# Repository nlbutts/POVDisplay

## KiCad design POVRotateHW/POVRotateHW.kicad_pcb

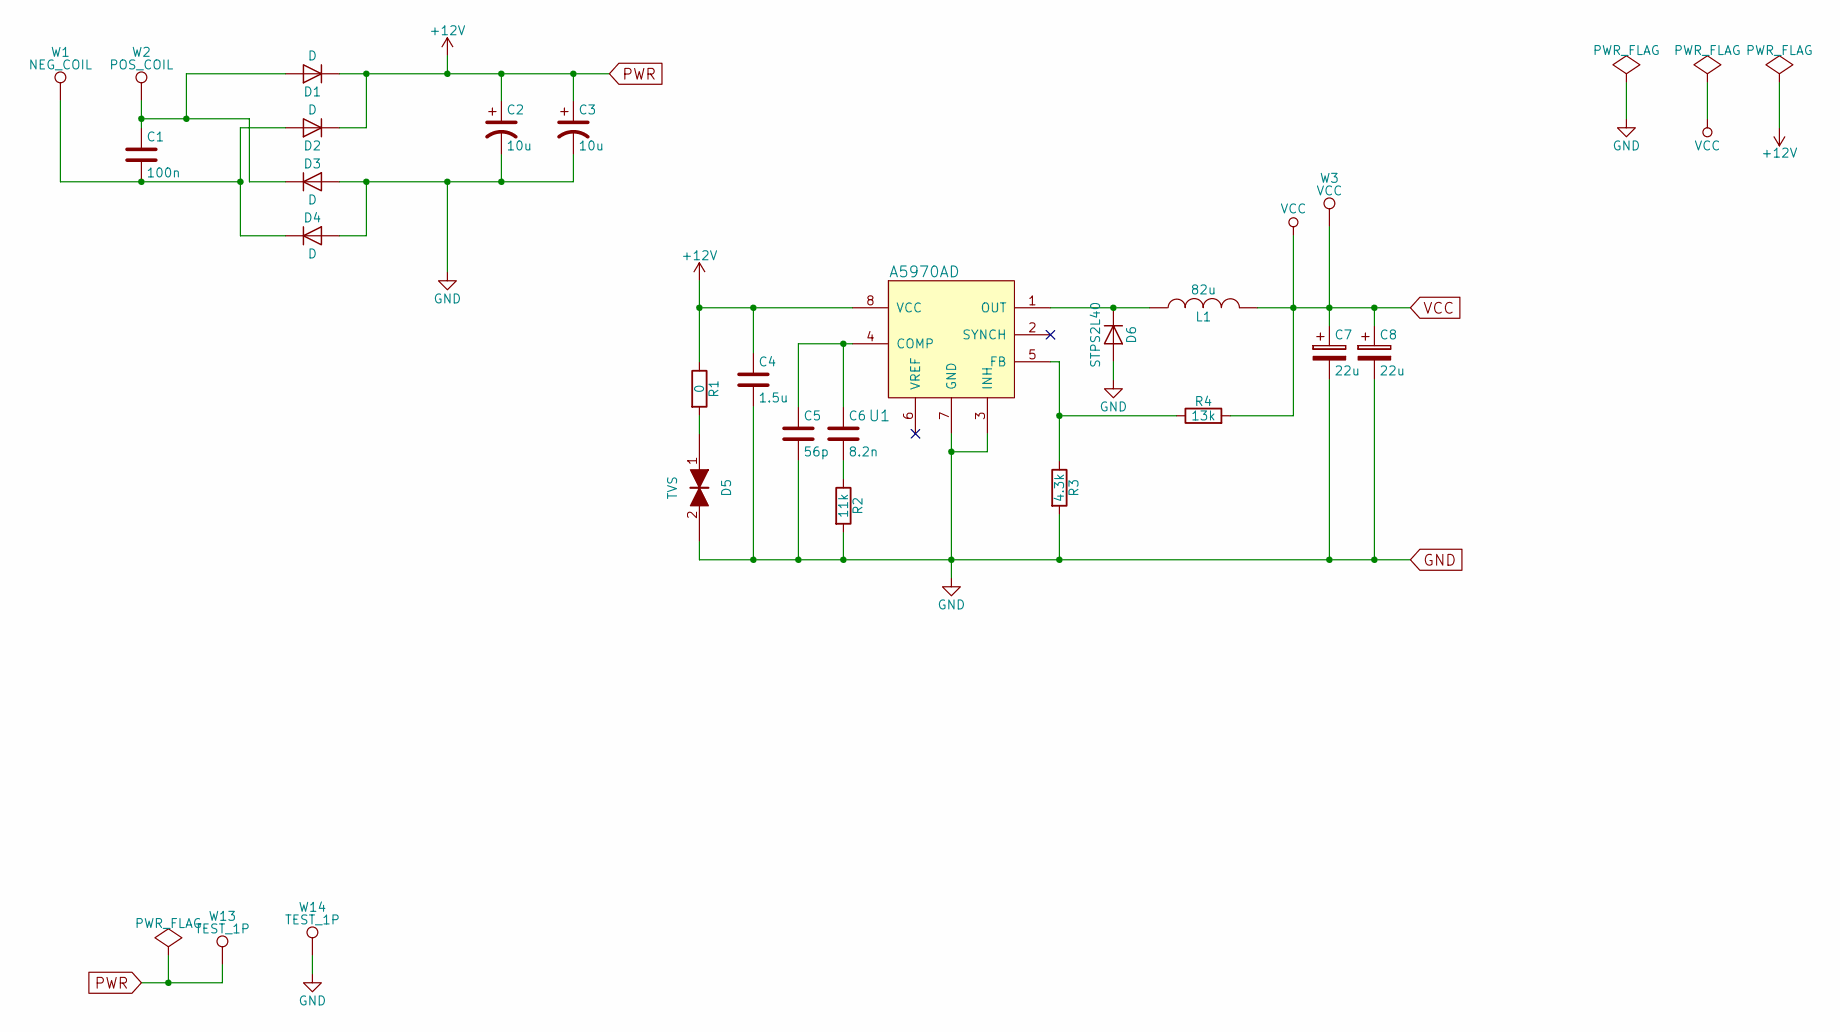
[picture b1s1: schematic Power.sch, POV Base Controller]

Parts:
C1: 100n; C_1210_HandSoldering
C2, C3: 10u; c_elec_5x5.8; PartNum EEE-FT1H220AR; DIGIKEY PCE5022CT-ND
C4: 1.5u; C_0805_HandSoldering; DIGIKEY 445-12701-1-ND
C5: 56p; C_0603_HandSoldering
C6: 8.2n; C_0603_HandSoldering
C7, C8: 22u; SMD-1210_Pol; PartNum TPSB226K006R0375; DIGIKEY 478-9063-1-ND
D1, D2, D3, D4: D; SMB_Handsoldering; PartNum STPS2L40U; DIGIKEY 497-5574-1-ND
D5: TVS; SMB_Handsoldering; PartNum 824520201; DIGIKEY 732-9779-1-ND
D6: STPS2L40; SMB_Handsoldering; PartNum STPS2L40U; DIGIKEY 497-5574-1-ND
L1: 82u; TDK_inductor_12.95x9.4x8.08; PartNum B82476A1104M; Digikey 495-2686-1-ND
R1: 0; R_0603_HandSoldering
R2: 11k; R_0603_HandSoldering
R3: 4.3k; R_0603_HandSoldering
R4: 13k; R_0603_HandSoldering
U1: A5970AD; SOIC-8-N; PartNum A5970ADTR; DIGIKEY 497-10183-1-ND
W1: NEG_COIL; MountingHole_3.2mm_M3_DIN965_Pad
W2: POS_COIL; MountingHole_3.2mm_M3_DIN965_Pad
W3: VCC; Measurement_Point_Round-SMD-Pad_Small
W13, W14: TEST_1P; Measurement_Point_Round-SMD-Pad_Small

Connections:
GND: C2.2, C3.2, C4.2, C5.2, C7.2, C8.2, D3.2 (A), D4.2 (A), D5.2, D6.2 (A), R2.2, R3.2, U1.3 (INH), U1.7 (GND), W14.1; also elsewhere on the board
unnamed: C1.1, D1.2 (A), D3.1 (K), W2.1
unnamed: C1.2, D2.2 (A), D4.1 (K), W1.1
unnamed: C5.1, C6.1, U1.4 (COMP)
unnamed: C6.2, R2.1
unnamed: D5.1, R1.2
unnamed: D6.1 (K), L1.1, U1.1 (OUT)
unnamed: R3.1, R4.1, U1.5 (FB)
PWR: C2.1, C3.1, C4.1, D1.1 (K), D2.1 (K), R1.1, U1.8 (VCC), W13.1; also elsewhere on the board
VCC: C7.1, C8.1, L1.2, R4.2, W3.1; also elsewhere on the board

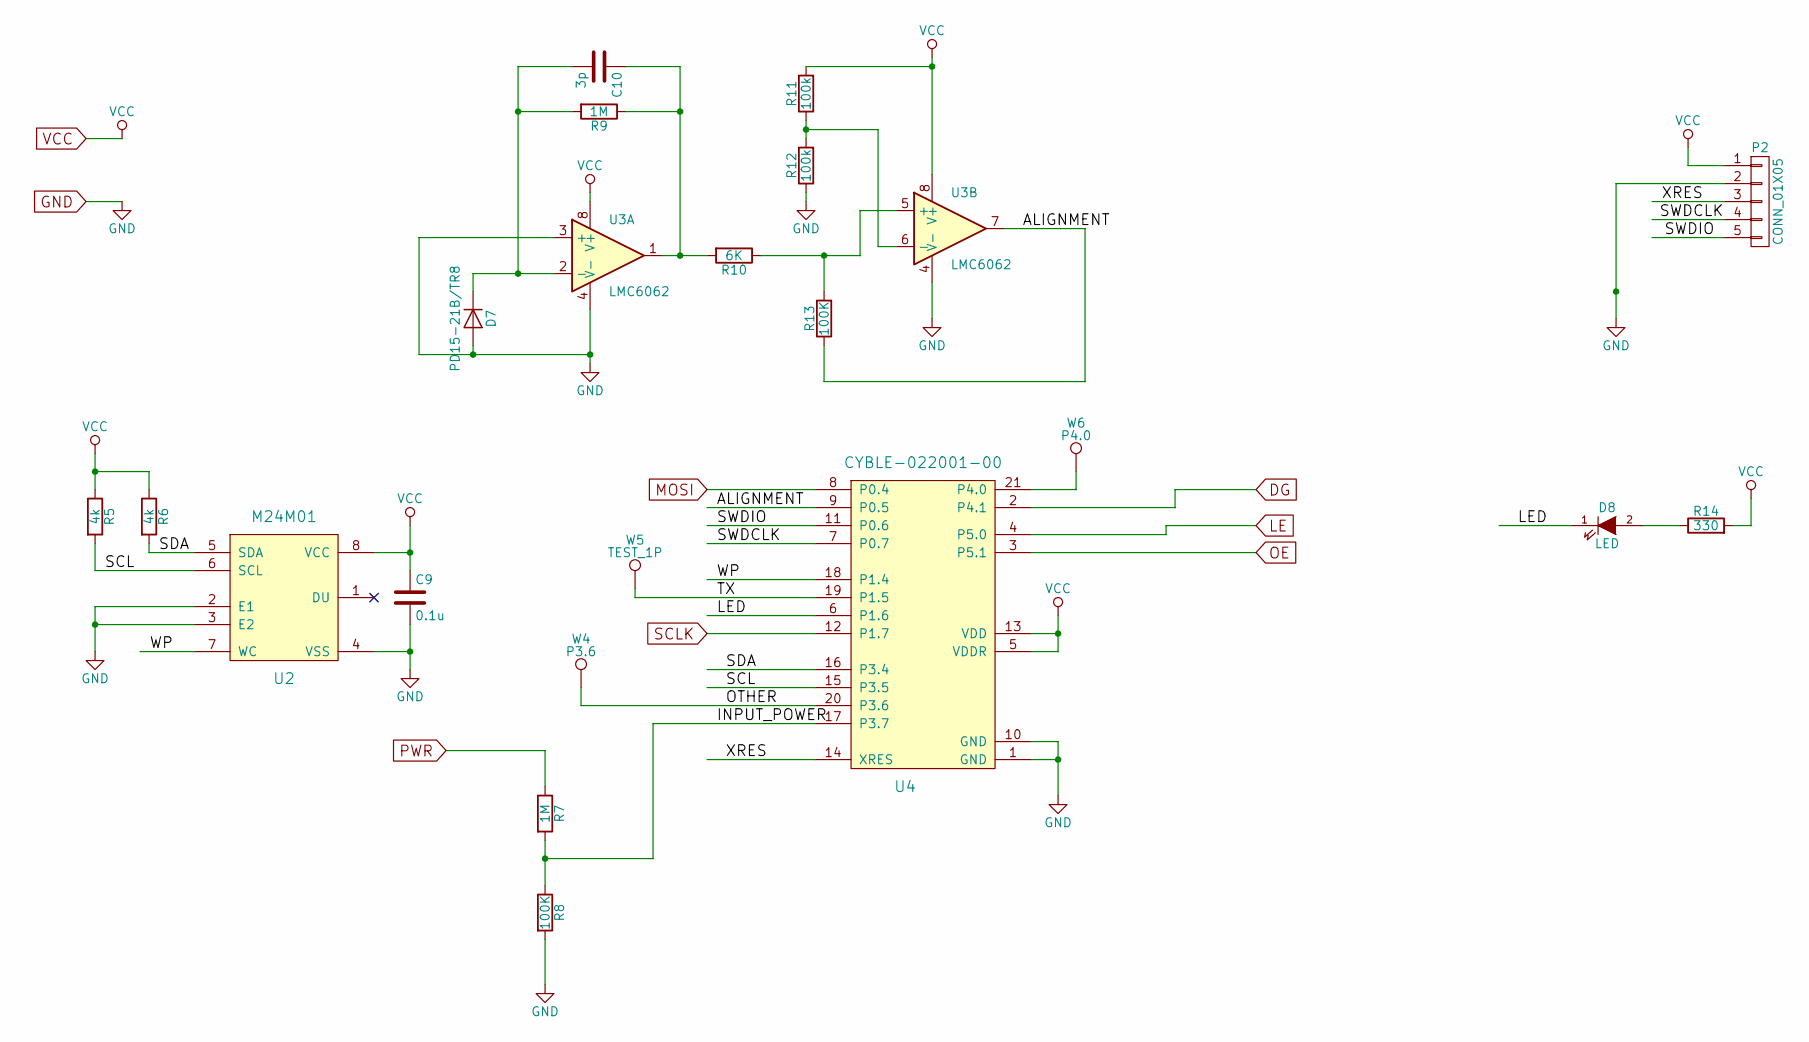
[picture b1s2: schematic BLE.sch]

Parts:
C9: 0.1u; C_0603_HandSoldering
C10: 3p; C_0603_HandSoldering
D7: PD15-21B/TR8; 2-SMD_Z-Bend; DIGIKEY 475-1346-1-ND
D8: LED; LED_0603; PartNum LG L29K-G2J1-24-Z; Digikey 475-2709-1-ND
P2: CONN_01X05; Socket_Strip_Straight_1x05
R5, R6: 4k; R_0603_HandSoldering
R7, R9: 1M; R_0603_HandSoldering
R8, R13: 100K; R_0603_HandSoldering
R10: 6K; R_0603_HandSoldering
R11, R12: 100k; R_0603_HandSoldering
R14: 330; R_0603_HandSoldering
U2: M24M01; SOIC-8-N; PartNum M24M01-RMN6TP; DIGIKEY 497-6351-1-ND
U3: LMC6062; SOIC-8-N; DIGIKEY LMC6032IMX/NOPBCT-ND
U4: CYBLE-022001-00; CYBLE-022001; PartNum CYBLE-022001-00; DIGIKEY 428-3566-PROMO-ND
W4: P3.6; Measurement_Point_Round-SMD-Pad_Small
W5: TEST_1P; Measurement_Point_Round-SMD-Pad_Small
W6: P4.0; Measurement_Point_Round-SMD-Pad_Small

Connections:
/BLE/ALIGNMENT: R13.1, U3.7, U4.9 (P0.5)
/BLE/INPUT_POWER: R7.2, R8.1, U4.17 (P3.7)
/BLE/LED: D8.1 (K), U4.6 (P1.6)
/BLE/OTHER: U4.20 (P3.6), W4.1
/BLE/SCL: R5.2, U2.6 (SCL), U4.15 (P3.5)
/BLE/SDA: R6.2, U2.5 (SDA), U4.16 (P3.4)
/BLE/SWDCLK: P2.4, U4.7 (P0.7)
/BLE/SWDIO: P2.5, U4.11 (P0.6)
/BLE/TX: U4.19 (P1.5), W5.1
/BLE/WP: U2.7 (WC), U4.18 (P1.4)
/BLE/XRES: P2.3, U4.14 (XRES)
DG: U4.2 (P4.1); also elsewhere on the board
GND: C9.2, D7.2 (A), P2.2, R8.2, R12.1, U2.2 (E1), U2.3 (E2), U2.4 (VSS), U3.3 (+), U3.4 (V-), U4.1 (GND), U4.10 (GND); also elsewhere on the board
LE: U4.4 (P5.0); also elsewhere on the board
MOSI: U4.8 (P0.4); also elsewhere on the board
unnamed: C10.1, R9.1, R10.2, U3.1
unnamed: C10.2, D7.1 (K), R9.2, U3.2 (-)
unnamed: D8.2 (A), R14.1
unnamed: R10.1, R13.2, U3.5 (+)
unnamed: R11.1, R12.2, U3.6 (-)
unnamed: U4.21 (P4.0), W6.1
OE: U4.3 (P5.1); also elsewhere on the board
PWR: R7.1; also elsewhere on the board
SCLK: U4.12 (P1.7); also elsewhere on the board
VCC: C9.1, P2.1, R5.1, R6.1, R11.2, R14.2, U2.8 (VCC), U3.8 (V+), U4.5 (VDDR), U4.13 (VDD); also elsewhere on the board

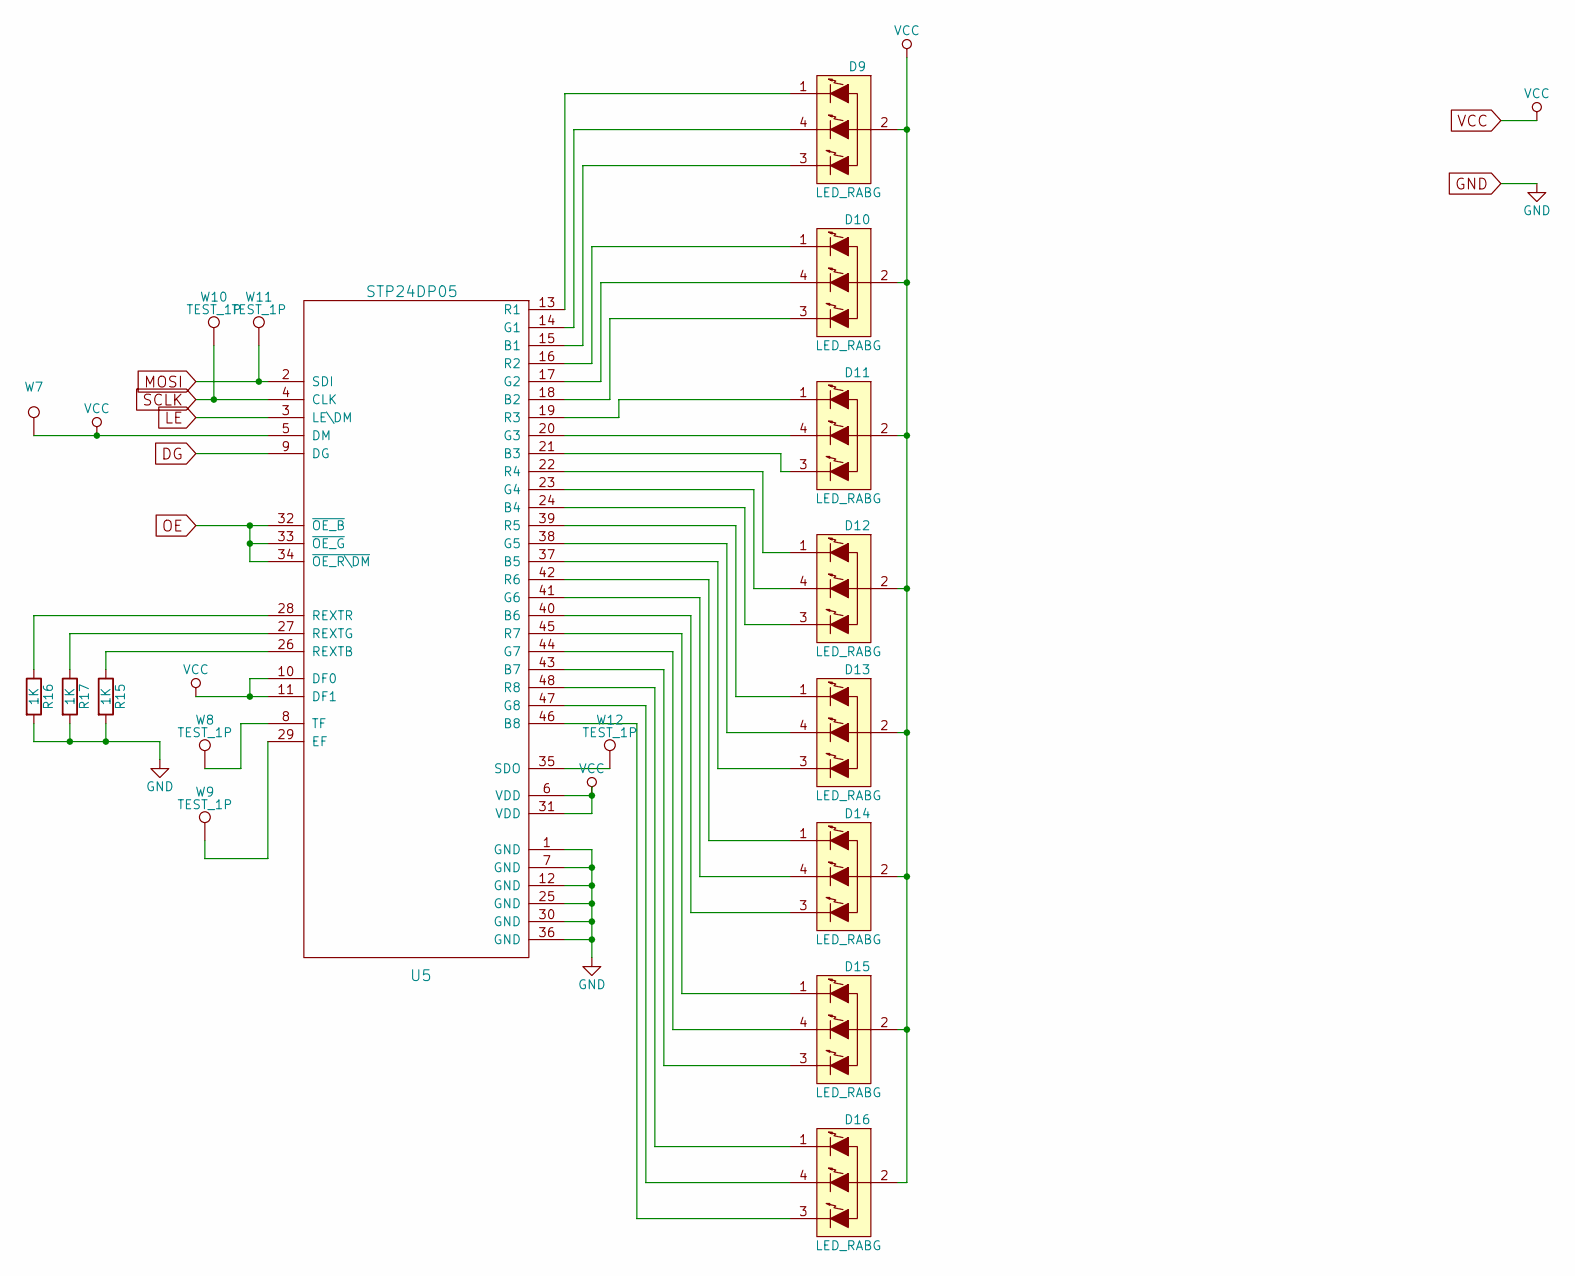
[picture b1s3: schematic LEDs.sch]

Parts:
D9: LED_RABG; CREE_PLCC4; PartNum CLV1A-FKB-CHMKPEHBB7A363; DIGIKEY CLV1A-FKB-CHMKPEHBB7A363CT-ND
D10, D11, D12, D13, D14, D15, D16: LED_RABG; CREE_PLCC4
R15, R16, R17: 1K; R_0805
U5: STP24DP05; TQFP-48_7x7mm_Pitch0.5mm; PartNum STP24DP05BTR; DIGIKEY 497-8283-1-ND
W7, W8, W9, W10, W11, W12: TEST_1P; Measurement_Point_Round-SMD-Pad_Small

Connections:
DG: U5.9 (DG); also elsewhere on the board
GND: R15.2, R16.2, R17.2, U5.1 (GND), U5.7 (GND), U5.12 (GND), U5.25 (GND), U5.30 (GND), U5.36 (GND); also elsewhere on the board
LE: U5.3 (LE\DM); also elsewhere on the board
MOSI: U5.2 (SDI), W11.1; also elsewhere on the board
unnamed: D9.1 (RED_CATHODE), U5.13 (R1)
unnamed: D9.3 (BLUE_CATHODE), U5.15 (B1)
unnamed: D9.4 (GREEN_CATHODE), U5.14 (G1)
unnamed: D10.1 (RED_CATHODE), U5.16 (R2)
unnamed: D10.3 (BLUE_CATHODE), U5.18 (B2)
unnamed: D10.4 (GREEN_CATHODE), U5.17 (G2)
unnamed: D11.1 (RED_CATHODE), U5.19 (R3)
unnamed: D11.3 (BLUE_CATHODE), U5.21 (B3)
unnamed: D11.4 (GREEN_CATHODE), U5.20 (G3)
unnamed: D12.1 (RED_CATHODE), U5.22 (R4)
unnamed: D12.3 (BLUE_CATHODE), U5.24 (B4)
unnamed: D12.4 (GREEN_CATHODE), U5.23 (G4)
unnamed: D13.1 (RED_CATHODE), U5.39 (R5)
unnamed: D13.3 (BLUE_CATHODE), U5.37 (B5)
unnamed: D13.4 (GREEN_CATHODE), U5.38 (G5)
unnamed: D14.1 (RED_CATHODE), U5.42 (R6)
unnamed: D14.3 (BLUE_CATHODE), U5.40 (B6)
unnamed: D14.4 (GREEN_CATHODE), U5.41 (G6)
unnamed: D15.1 (RED_CATHODE), U5.45 (R7)
unnamed: D15.3 (BLUE_CATHODE), U5.43 (B7)
unnamed: D15.4 (GREEN_CATHODE), U5.44 (G7)
unnamed: D16.1 (RED_CATHODE), U5.48 (R8)
unnamed: D16.3 (BLUE_CATHODE), U5.46 (B8)
unnamed: D16.4 (GREEN_CATHODE), U5.47 (G8)
unnamed: R15.1, U5.26 (REXTB)
unnamed: R16.1, U5.28 (REXTR)
unnamed: R17.1, U5.27 (REXTG)
unnamed: U5.8 (TF), W8.1
unnamed: U5.29 (EF), W9.1
unnamed: U5.35 (SDO), W12.1
OE: U5.32 (~OE_B), U5.33 (~OE_G), U5.34 (~OE_R\DM); also elsewhere on the board
SCLK: U5.4 (CLK), W10.1; also elsewhere on the board
VCC: D9.2 (COMMON_ANODE), D10.2 (COMMON_ANODE), D11.2 (COMMON_ANODE), D12.2 (COMMON_ANODE), D13.2 (COMMON_ANODE), D14.2 (COMMON_ANODE), D15.2 (COMMON_ANODE), D16.2 (COMMON_ANODE), U5.5 (DM), U5.6 (VDD), U5.10 (DF0), U5.11 (DF1), U5.31 (VDD), W7.1; also elsewhere on the board

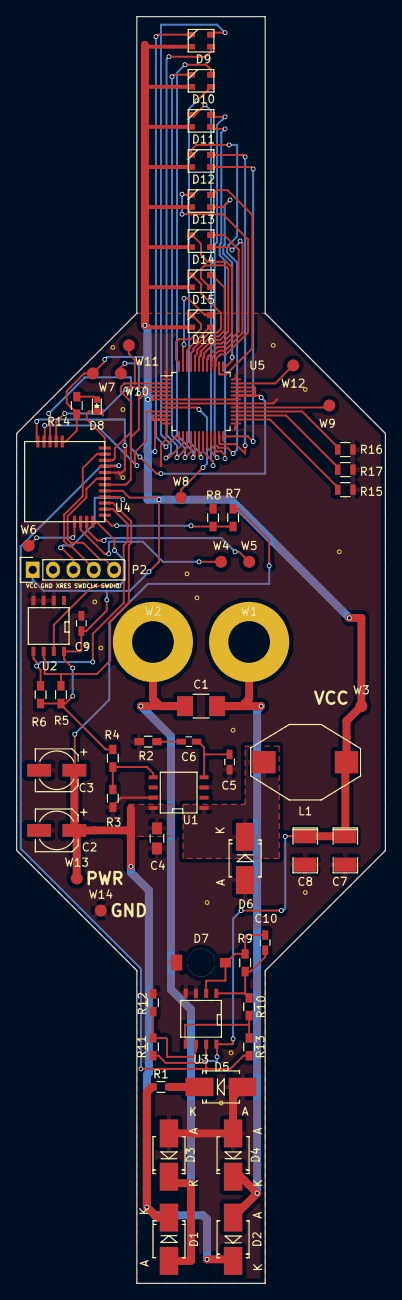
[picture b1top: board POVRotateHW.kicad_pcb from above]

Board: 2 copper layers, 46.0 x 158.0 mm, 64 parts (0 on the bottom side), 62 nets.

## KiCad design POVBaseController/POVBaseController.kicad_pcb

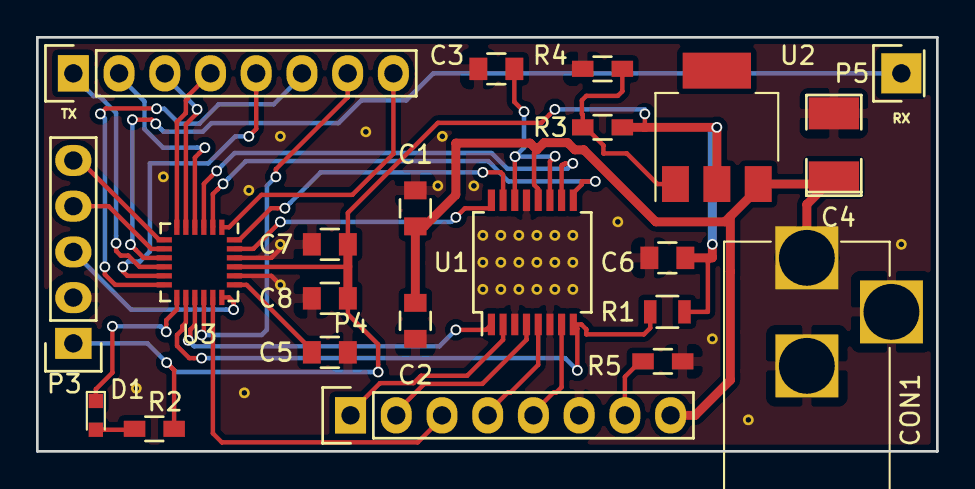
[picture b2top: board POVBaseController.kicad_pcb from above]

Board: 2 copper layers, 50.0 x 23.0 mm, 22 parts (0 on the bottom side), 32 nets.

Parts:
C1, C5, C8: 0.1u; C_0805
C2: 10u; C_0805
C3: 2.2u; C_0805
C4: 10u; SMD-1210_Pol
C6, C7: 1u; C_0805
CON1: BARREL_JACK
D1: LED; LED_0603
P2, P4: CONN_01X08; Socket_Strip_Straight_1x08
P3: CONN_01X05; Socket_Strip_Straight_1x05
P5: CONN_01X01; Socket_Strip_Straight_1x01
R1: 10K; R_0805
R2: 330; R_0603_HandSoldering
R3: 120; R_0603_HandSoldering
R4: 360; R_0603_HandSoldering
R5: 1.5k; R_0603_HandSoldering
U1: DRV8848; SSOP-16_5.3x6.2mm_Pitch0.65mm
U2: LM317AEMP; SOT-223
U3: CY8C4024LQI-S401; QFN-24_4x4mm_Pitch0.5mm

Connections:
+12V: C1.2, C2.2, C4.1, CON1.1, P4.8, U1.12, U2.3
/COIL_IN_A: U1.9, U3.2
/COIL_IN_B: U1.10, U3.3
/COIL_OUT_A: P4.5, U1.7
/COIL_OUT_B: P4.4, U1.5
/LED: D1.1, U3.13
/MOTOR_IN_A: U1.16, U3.23
/MOTOR_IN_B: U1.15, U3.24
/MOTOR_OUT_A: P4.1, U1.2
/MOTOR_OUT_B: P4.2, U1.4
/NIR_EMITTER: P4.7, R5.1
/SPARE_1: P2.2, U3.4
/SPARE_2: P2.3, U3.5
/SPARE_3: P2.4, U3.6
/SPARE_4: P2.5, U3.11
/SPARE_5: P2.6, U3.12
/SPARE_6: P2.7, U3.16
/SPARE_7: P2.8, U3.1
/SPARE_8: P4.3, U3.17
/SWDCLK: P3.4, U3.8
/SWDIO: P3.5, U3.7
/UART_RX: P5.1, U3.9
/UART_TX: P2.1, U3.10
/XRES: P3.3, U3.18
/nFAULT: R1.2, U1.8, U3.14
/nSLEEP: U1.1, U3.15
GND: C1.1, C2.1, C3.1, C4.2, C5.2, C6.2, C7.2, C8.2, CON1.2, CON1.3, P3.2, P4.6, R4.2, R5.2, U1.3, U1.6, U1.13, U3.20, U3.22
unnamed: C3.2, U1.11, U1.14
unnamed: C5.1, U3.19
unnamed: D1.2, R2.1
unnamed: R3.2, R4.1, U2.1
VCC: C6.1, C7.1, C8.1, P3.1, R1.1, R2.2, R3.1, U2.2, U3.21

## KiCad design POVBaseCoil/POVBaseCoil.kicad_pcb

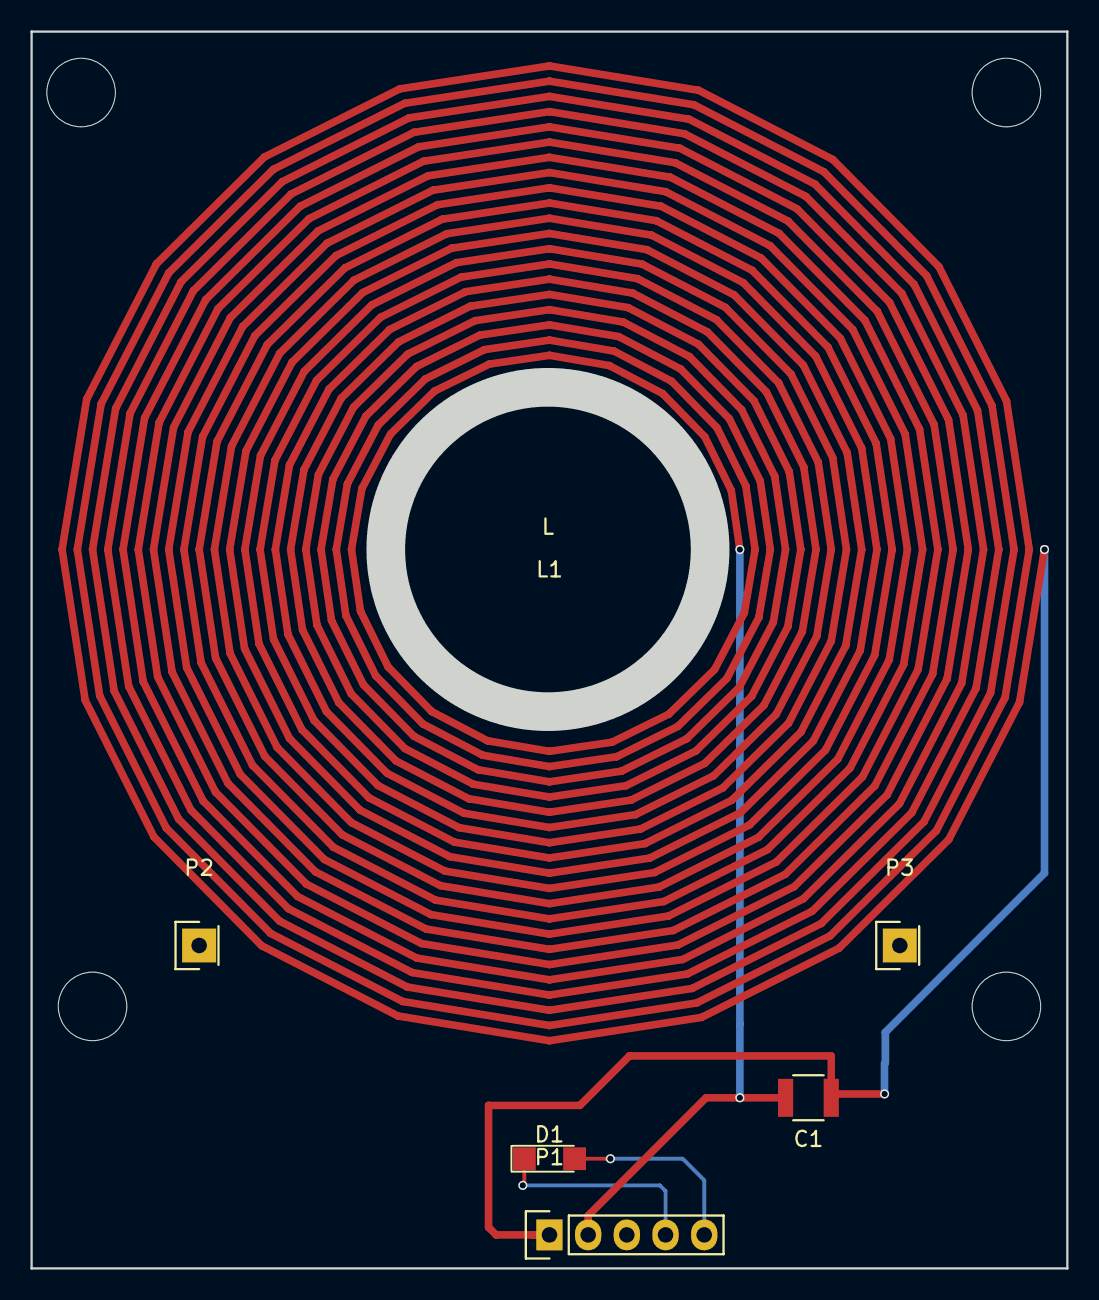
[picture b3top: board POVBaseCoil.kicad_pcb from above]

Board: 2 copper layers, 65.6 x 78.8 mm, 6 parts (0 on the bottom side), 4 nets.

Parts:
C1: C; C_1210
D1: LED; LED_1206
L1: L; pov_coil
P1: CONN_01X05; Socket_Strip_Straight_1x05
P2, P3: CONN_01X01; Socket_Strip_Straight_1x01

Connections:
unnamed: C1.1, L1.1, P1.1
unnamed: C1.2, L1.2, P1.2
unnamed: D1.1, P1.4
unnamed: D1.2, P1.5

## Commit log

2016-05-25 Checked in the compiler.
2016-05-30 Refactor the toolchain.
2016-05-30 Moved toolchain.
2016-06-01 Copied in the USB drivers, and the HAL stuff.
2016-06-01 more updates.
2016-06-04 First version that compiles.
2016-06-04 Code runs, but LED seems to be backwards and the fan signal doesn't seem to work.
2016-09-26 Removed the old POVbase
2016-09-26 Updated to the new POV Display project style.
2016-09-27 Added mylib
2016-09-27 Updated the design and layout with an LDO.
2016-09-29 Updated design to use an ST switcher.
2016-09-29 Completed the routing of the POVBaseController.
2016-09-29 Ordering the POVBaseController
2016-10-04 Minor updates.
2016-10-27 Added the POVRate HW
2016-10-27 Started working on the schematic for the POV Rotate board.
2016-10-28 Added the reusable library.
2016-10-31 Connected some pins up.
2016-10-31 Finished the schematic for the POVRotate system, started on layout.
2016-11-01 Started work on the POV Rotate layout.
2016-11-02 Moved parts around.
2016-11-03 Working on PCB placement.
2016-11-03 Updated the designs ref des to the LEDs work.
2016-11-04 Finished routing board. Need to do another once over.
2016-11-05 Updated the 3D shapes. Debating if I should try and squish the design into a smaller form factor.
2016-11-09 Added silk screen.
2016-12-01 Minor updates based on the actual PCB.
2016-12-02 Rerouting board for RevB
2016-12-05 Added the EEPROM library and issues.txt
2016-12-07 Switched the LED driver to a 24-bit LED driver from ST.
2016-12-07 Starting layout on the new design.
2016-12-07 Worked on routing the LEDs.
2016-12-08 The routing is almost complete.
2016-12-08 Finished the routing.
2016-12-09 Completed layout and updates to silk screen.
2016-12-09 Order the boards.
2016-12-11 Added a 3D drawing. Added a POVBase with an HBridge.
2016-12-14 Updated the mechanical mount.
2016-12-20 Added the PCB Motor mount. Removed the STL files.
2016-12-20 Updated mechanical components.
2016-12-28 Updated schematic and removed some old datasheets.
2016-12-28 Added additional datasheets and LED code.
2016-12-31 Updates. Everything (except the EEPROM) is now working.
2016-12-31 Added the EEPROM library and the UART_TO_BLE_Peripherial.
2016-12-31 Added the BLE code to create a UART interface
2016-12-31 Updated the gitignore file and added the datasheet for the LEDs.
2017-01-02 It works. The POV Display is working and displaying 4 color quads. Next step, a second hand.
2017-01-03 More updates. I have a sydstem that now displays a one second time as well as a crazy pattern.
2017-01-04 Updated the mechanical components.
2017-01-05 Started to work on the POV Base Controller.
2017-01-06 Updated the POVBaseController schematic. Adding the DRV8848.
2017-01-06 More work on the new base controller.
2017-01-06 Added the DRV8848 datasheet.
2017-01-07 Finished the POV H-Bridge controller schematic and working on layout.
2017-01-08 Finished the layout of the POV Base Controller.
2017-01-08 Added the start of the new base coil.
2017-01-08 Totally refactored the POV Base Controller.
2017-01-09 Completed the POV Base coil.
2017-01-09 Updated the motor mount. I got it wrong... again.
2017-01-23 Ordered the POV Base Controller and the POV Base Coil.
2017-01-23 Added some fonts.
2017-01-29 Updates to for drawing the clock. Now generates 120 updates per rotation. Average update loop takes 31 us.
2017-01-29 I am able to display Hello
2017-01-31 Updated the designs with better cutouts and 3D parts.
2017-01-31 Started work on a combined mechanical part.
2017-02-01 Updated the main mechanical layout
2017-02-02 Have a working clock. Need to sync it with an Android app.
2017-02-07 Started implementing RTC for the POV Display. Tried using DesignSpark MEchanical to design mounts.
2017-02-20 Tried to update the mechanical components.
2017-03-05 Created a main mount for the new Base boards.
2017-03-23 Added date display, updated mechanical designs.
2017-03-23 Added a device to balance the wobble.
2017-03-26 Added additional code for BLE. Can set time, see speed, change filter coeff.
2017-03-29 Checked in app
2017-03-31 Updated the app to read write everything from the display. Just need to get notifications working.
2017-04-03 Trying to get notifications and the time sync working.
2018-04-07 Made some changes to the code to display a clock. Started to refactor the main mount.
2018-04-08 Design is working and I can correctly offset the time.
2018-04-08 Added mounts that will be used to bolt the unit down to wood.
2018-04-08 Got gitfucked again. Had to manually fix files.
2018-04-08 Final working version.
2018-04-08 Added the android project.

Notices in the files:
POVBaseCoil/POVBaseCoil.kicad_pcb:
Copyright 2017
POVRotateHW/POVRotateHW.kicad_pcb:
Copyright 2016
